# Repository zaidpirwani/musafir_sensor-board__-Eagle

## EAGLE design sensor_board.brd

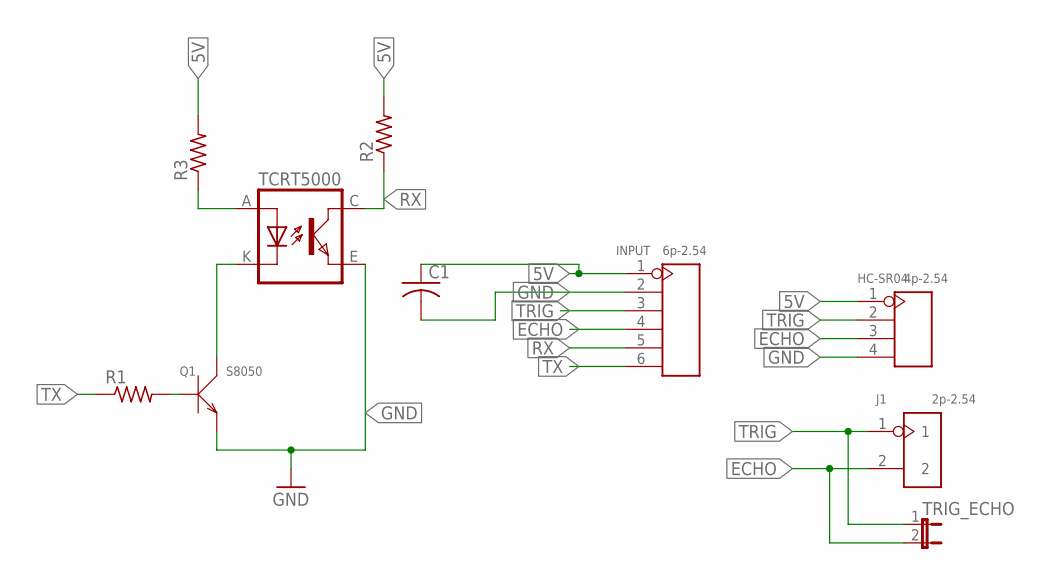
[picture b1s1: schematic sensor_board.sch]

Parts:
C1: C-USC1206; C1206
HC-SR04: 4p-2.54; H4-2.54
INPUT: 6p-2.54; H6-2.54
J1: 2p-2.54; H2-2.54
Q1: S8050; SOT-23
R1, R2, R3: R-US_R1206; R1206
TCRT5000: TCRT5000
TRIG_ECHO: JUMPER-2SMD-NC; SJ_2S

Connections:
5V: C1.1, HC-SR04.1, INPUT.1, R2.2, R3.2
ECHO: HC-SR04.3, INPUT.4, J1.2, TRIG_ECHO.2
GND: C1.2, HC-SR04.4, INPUT.2, Q1.2 (E), TCRT5000.E (EMITTER)
unnamed: R3.1, TCRT5000.A (ANODE)
unnamed: Q1.3 (C), TCRT5000.K (CATHODE)
unnamed: Q1.1 (B), R1.2
RX: INPUT.5, R2.1, TCRT5000.C (COLLECTOR)
TRIG: HC-SR04.2, INPUT.3, J1.1, TRIG_ECHO.1
TX: INPUT.6, R1.1

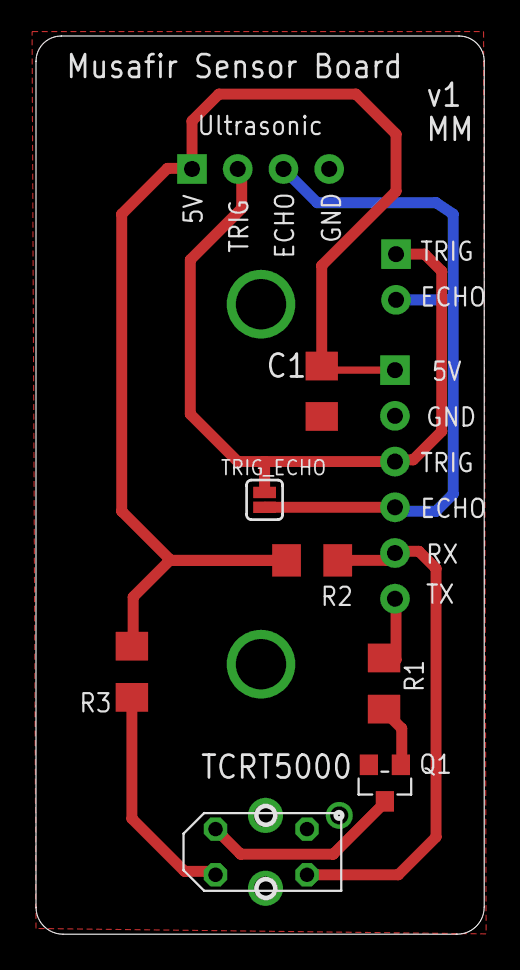
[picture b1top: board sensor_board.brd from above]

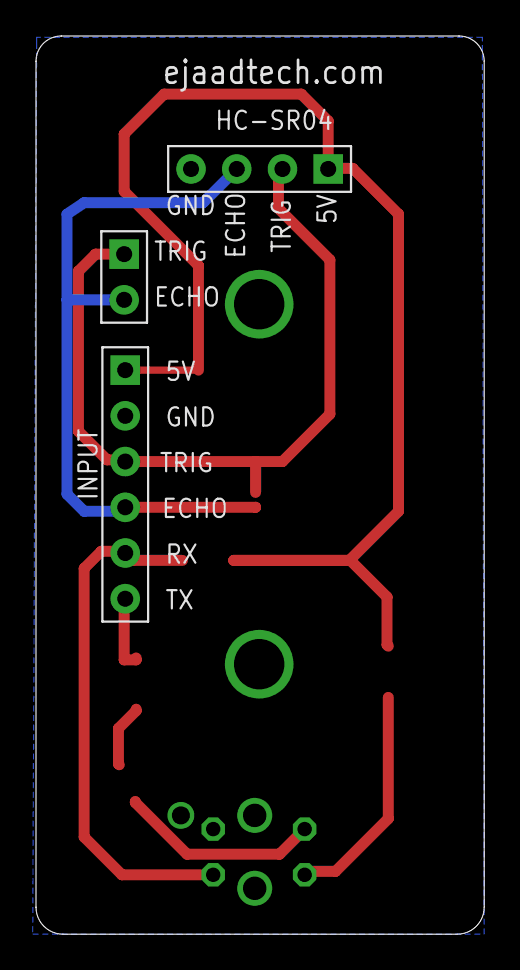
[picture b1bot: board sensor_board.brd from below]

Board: 2 copper layers, 24.9 x 49.9 mm, 10 parts (3 on the bottom side), 9 nets.

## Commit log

2016-06-30 PCB cosmetic changes
    now, READY for sensing to SEEED for v1 fabrication.

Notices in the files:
parts and their libraries:
SparkFun-Retired: Licensing:Creative Commons ShareAlike 4.0 International - https://creativecommons.org/licenses/by-sa/4.0
